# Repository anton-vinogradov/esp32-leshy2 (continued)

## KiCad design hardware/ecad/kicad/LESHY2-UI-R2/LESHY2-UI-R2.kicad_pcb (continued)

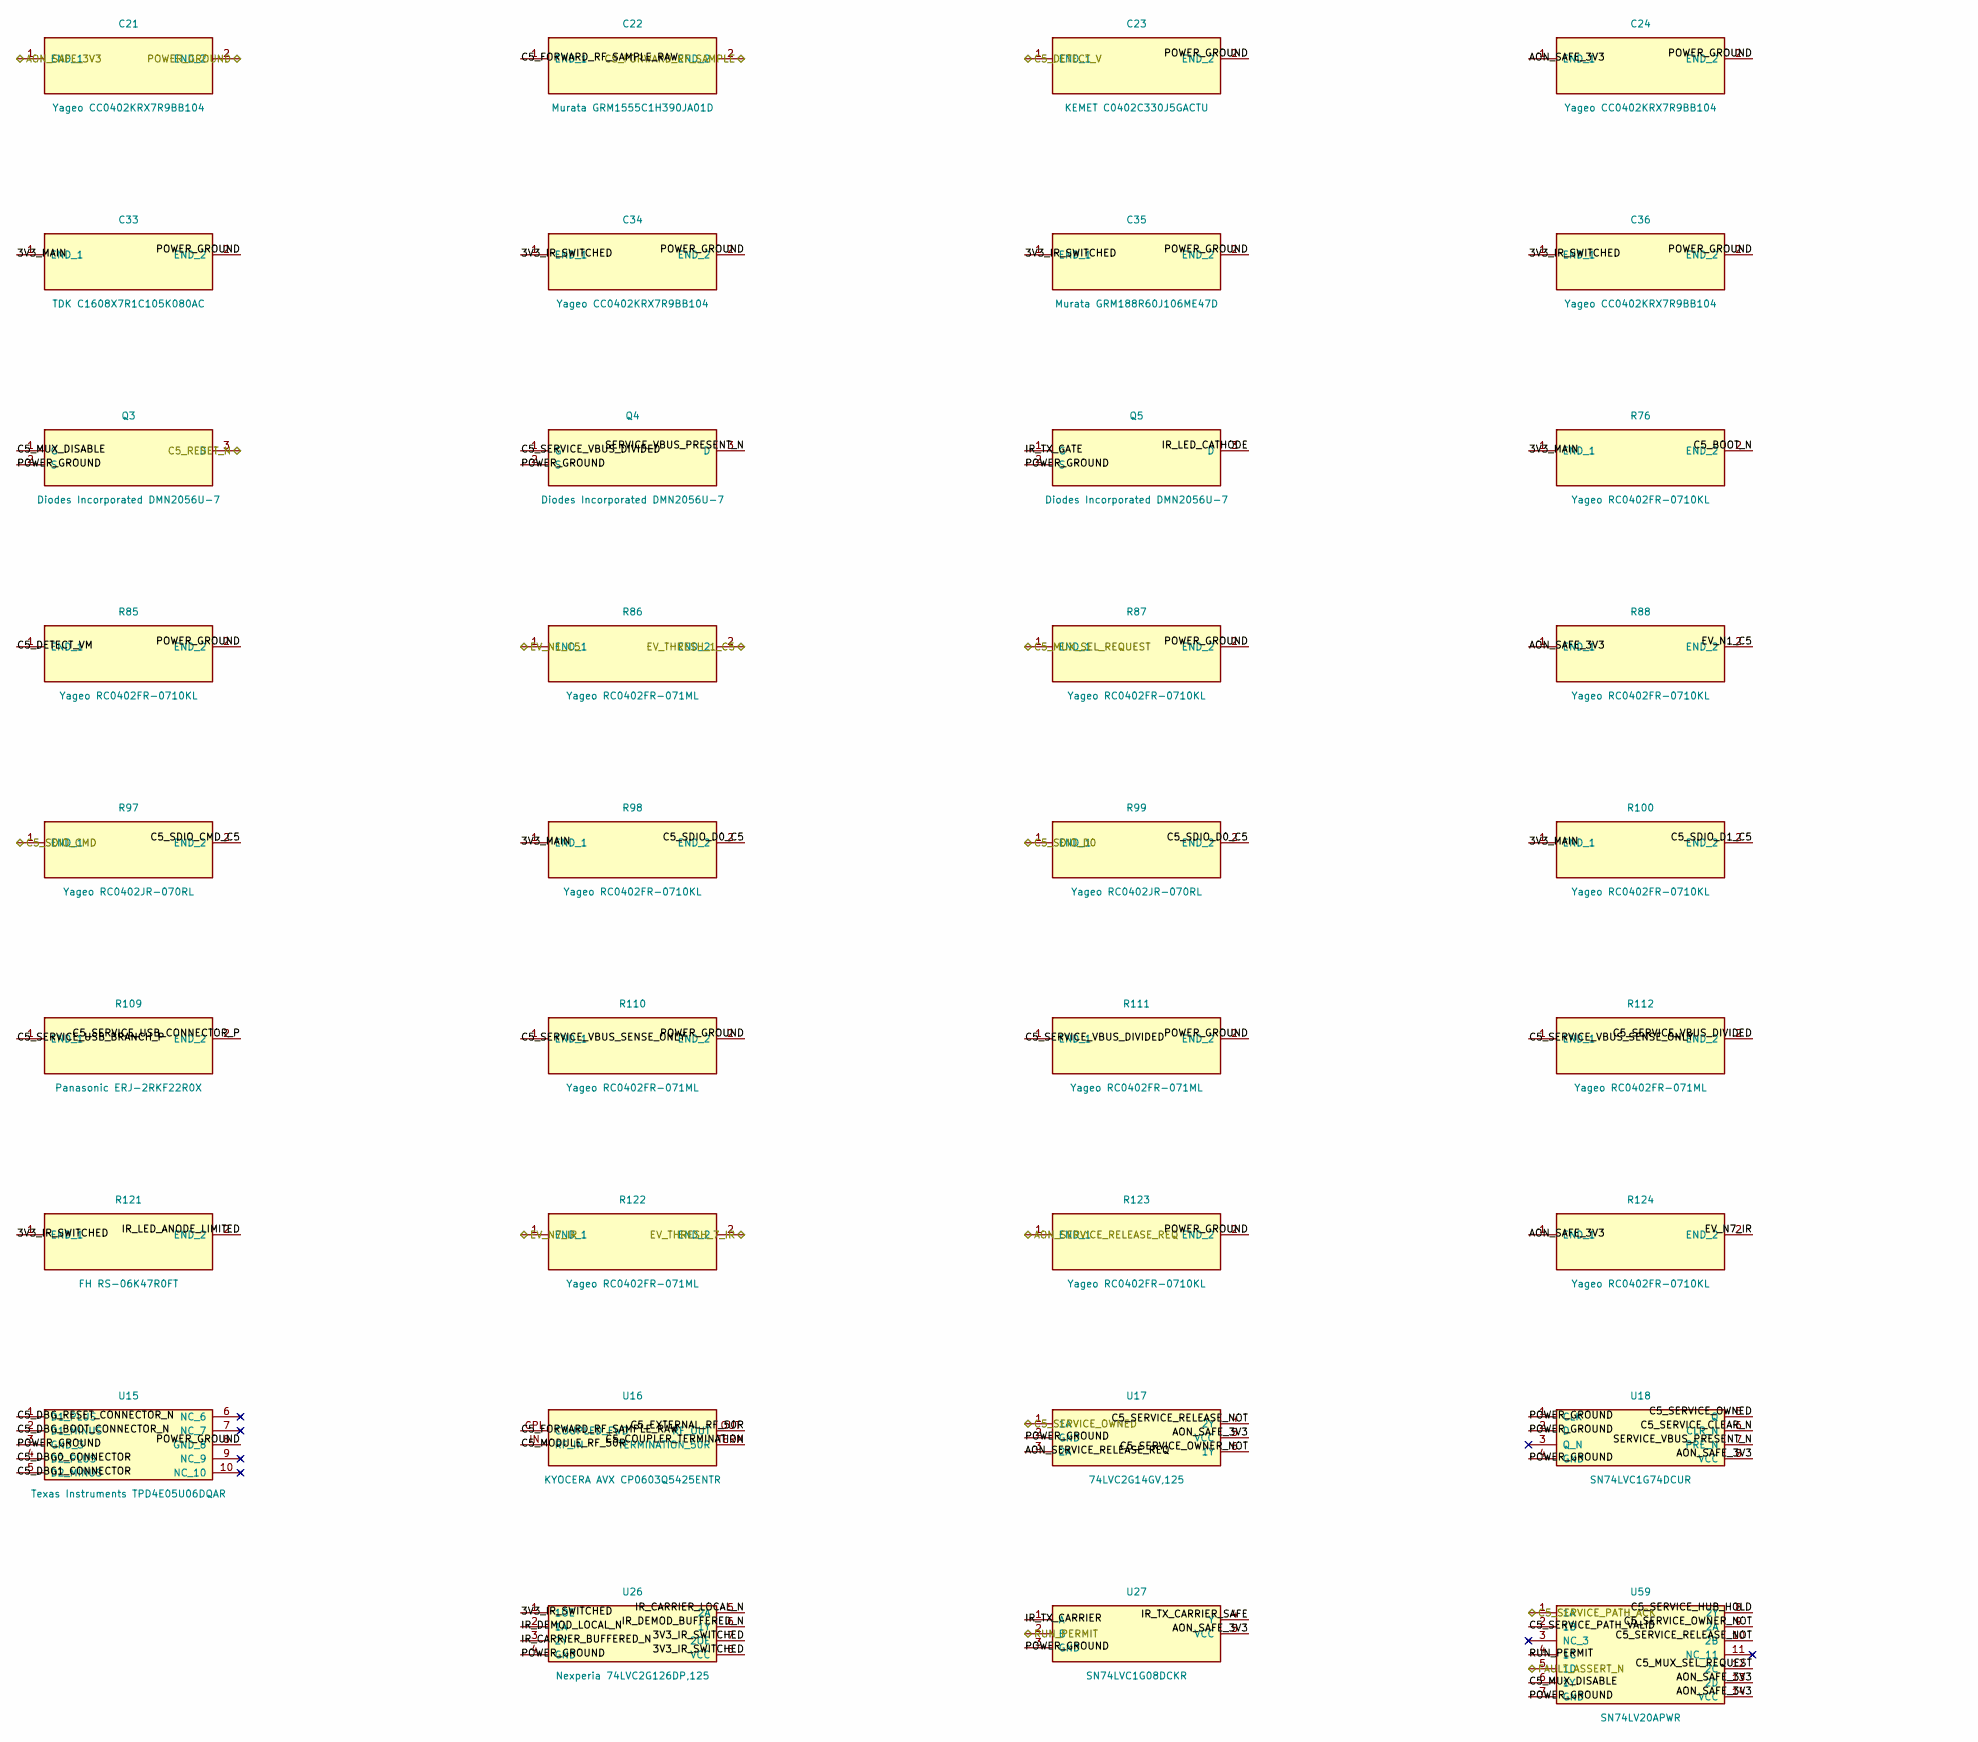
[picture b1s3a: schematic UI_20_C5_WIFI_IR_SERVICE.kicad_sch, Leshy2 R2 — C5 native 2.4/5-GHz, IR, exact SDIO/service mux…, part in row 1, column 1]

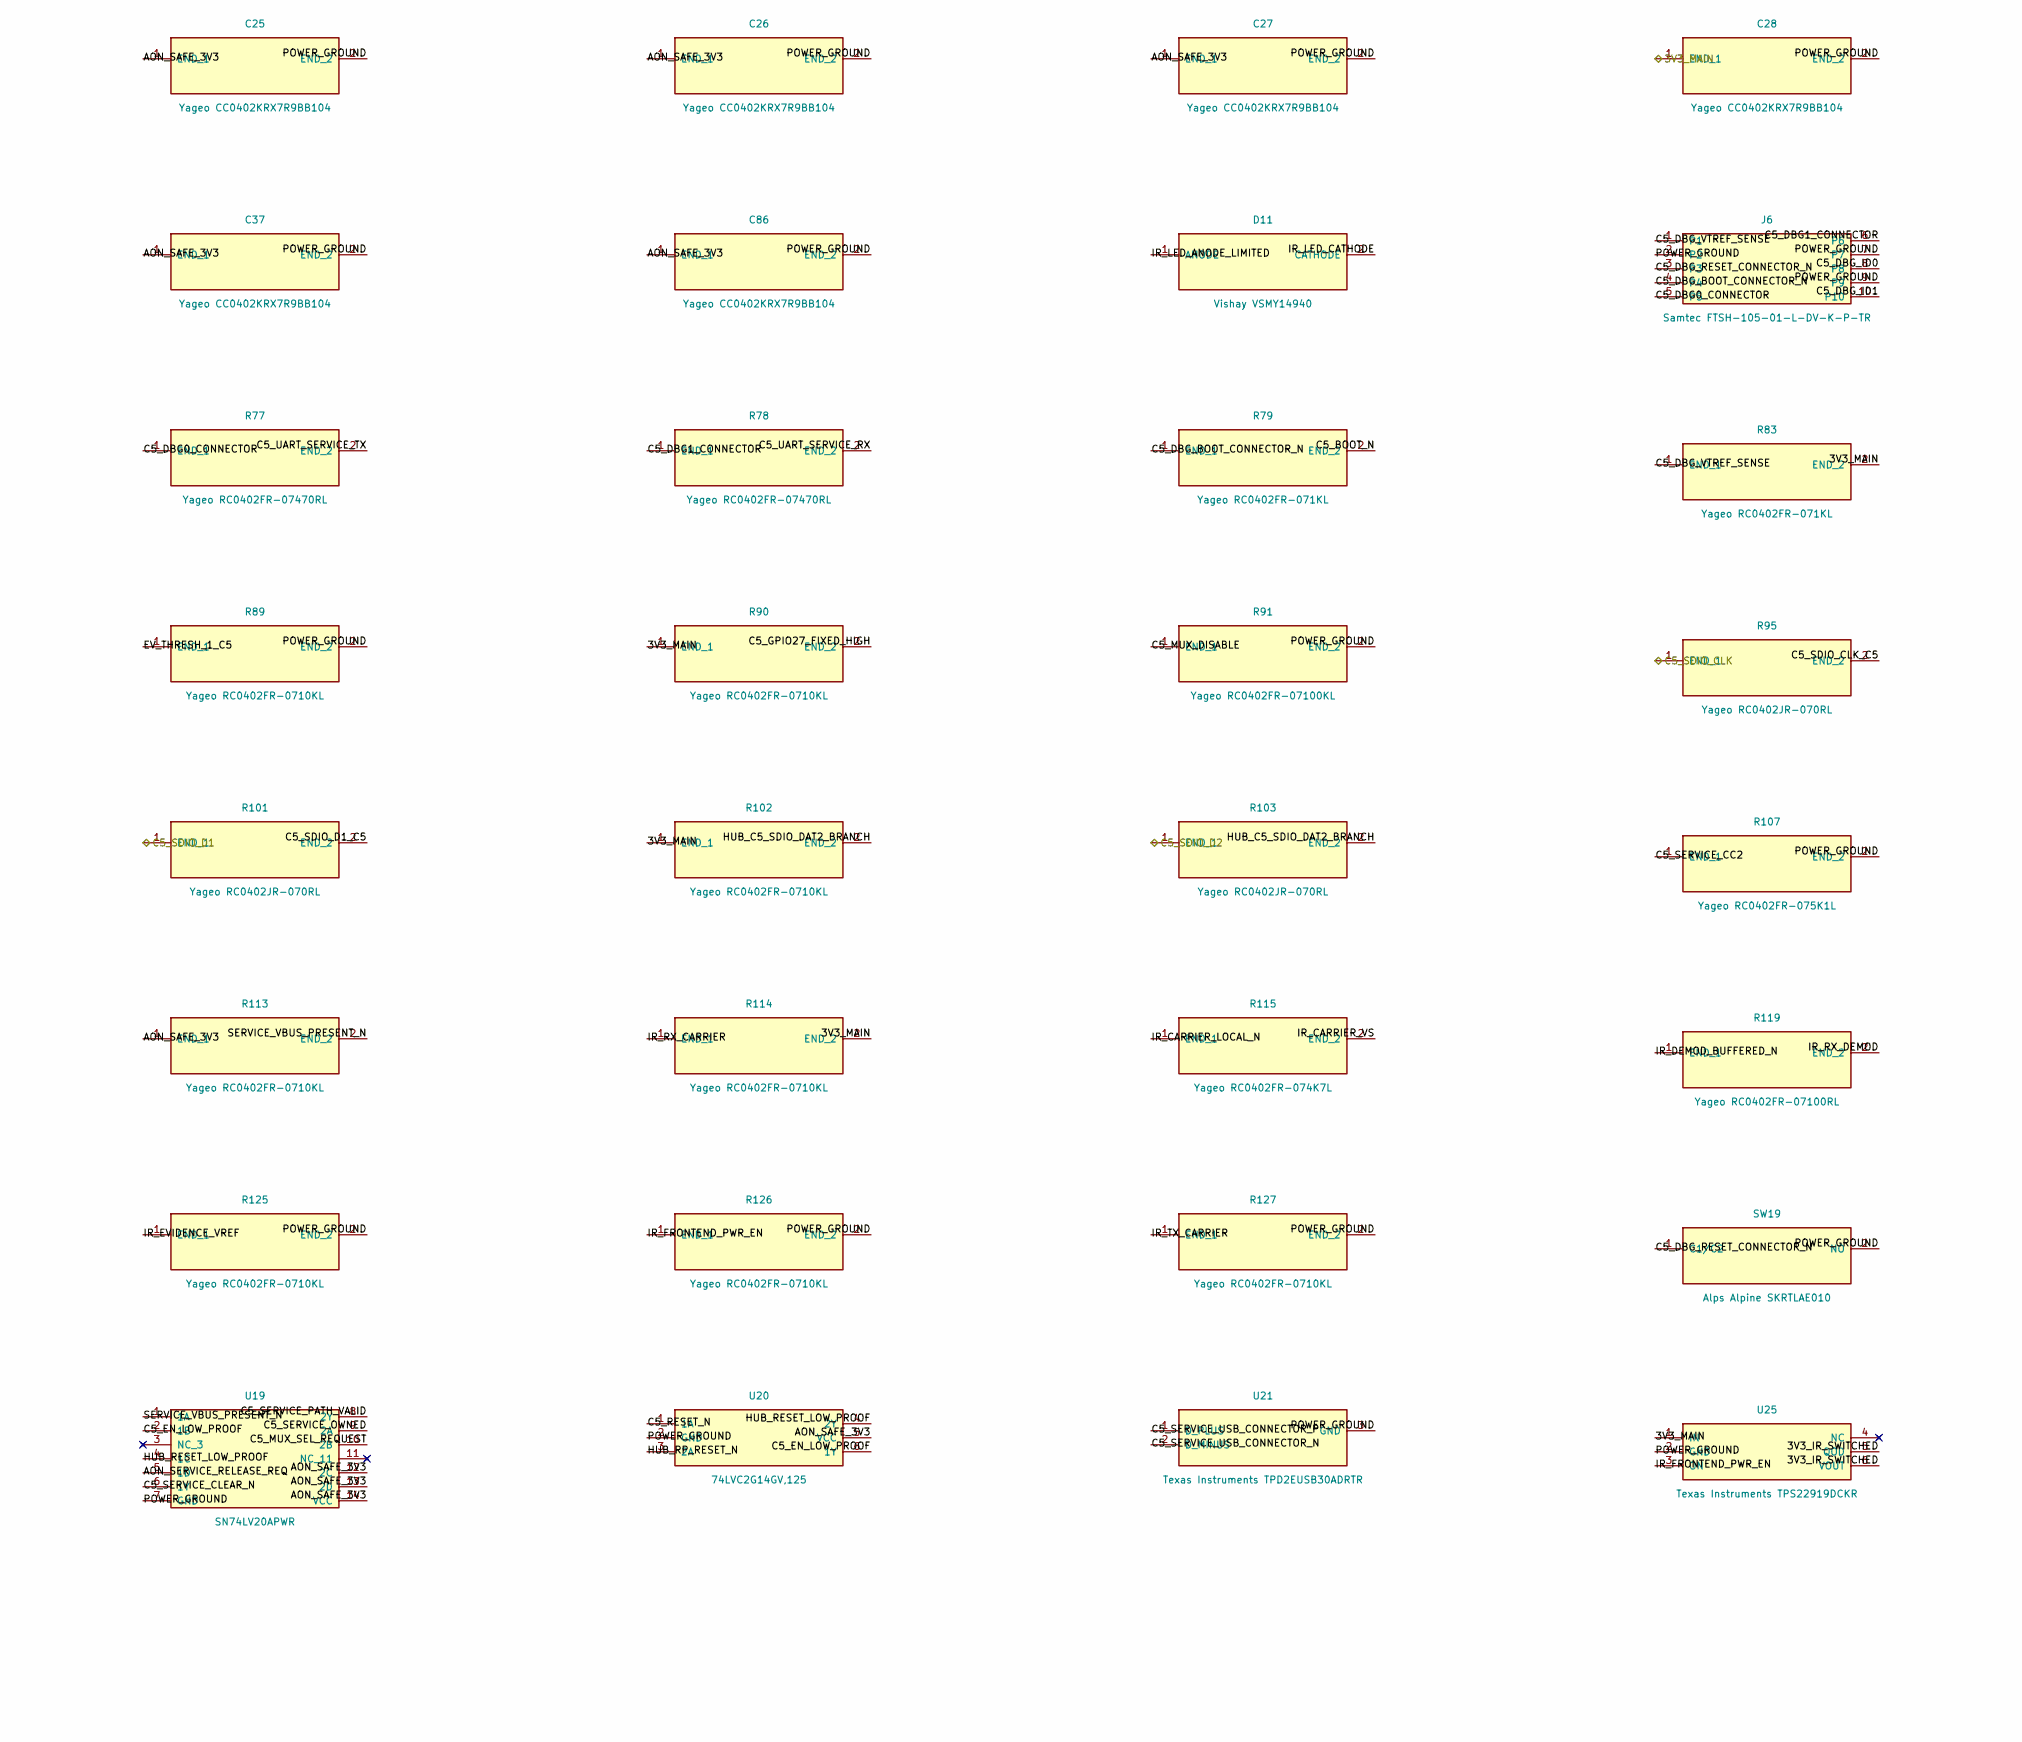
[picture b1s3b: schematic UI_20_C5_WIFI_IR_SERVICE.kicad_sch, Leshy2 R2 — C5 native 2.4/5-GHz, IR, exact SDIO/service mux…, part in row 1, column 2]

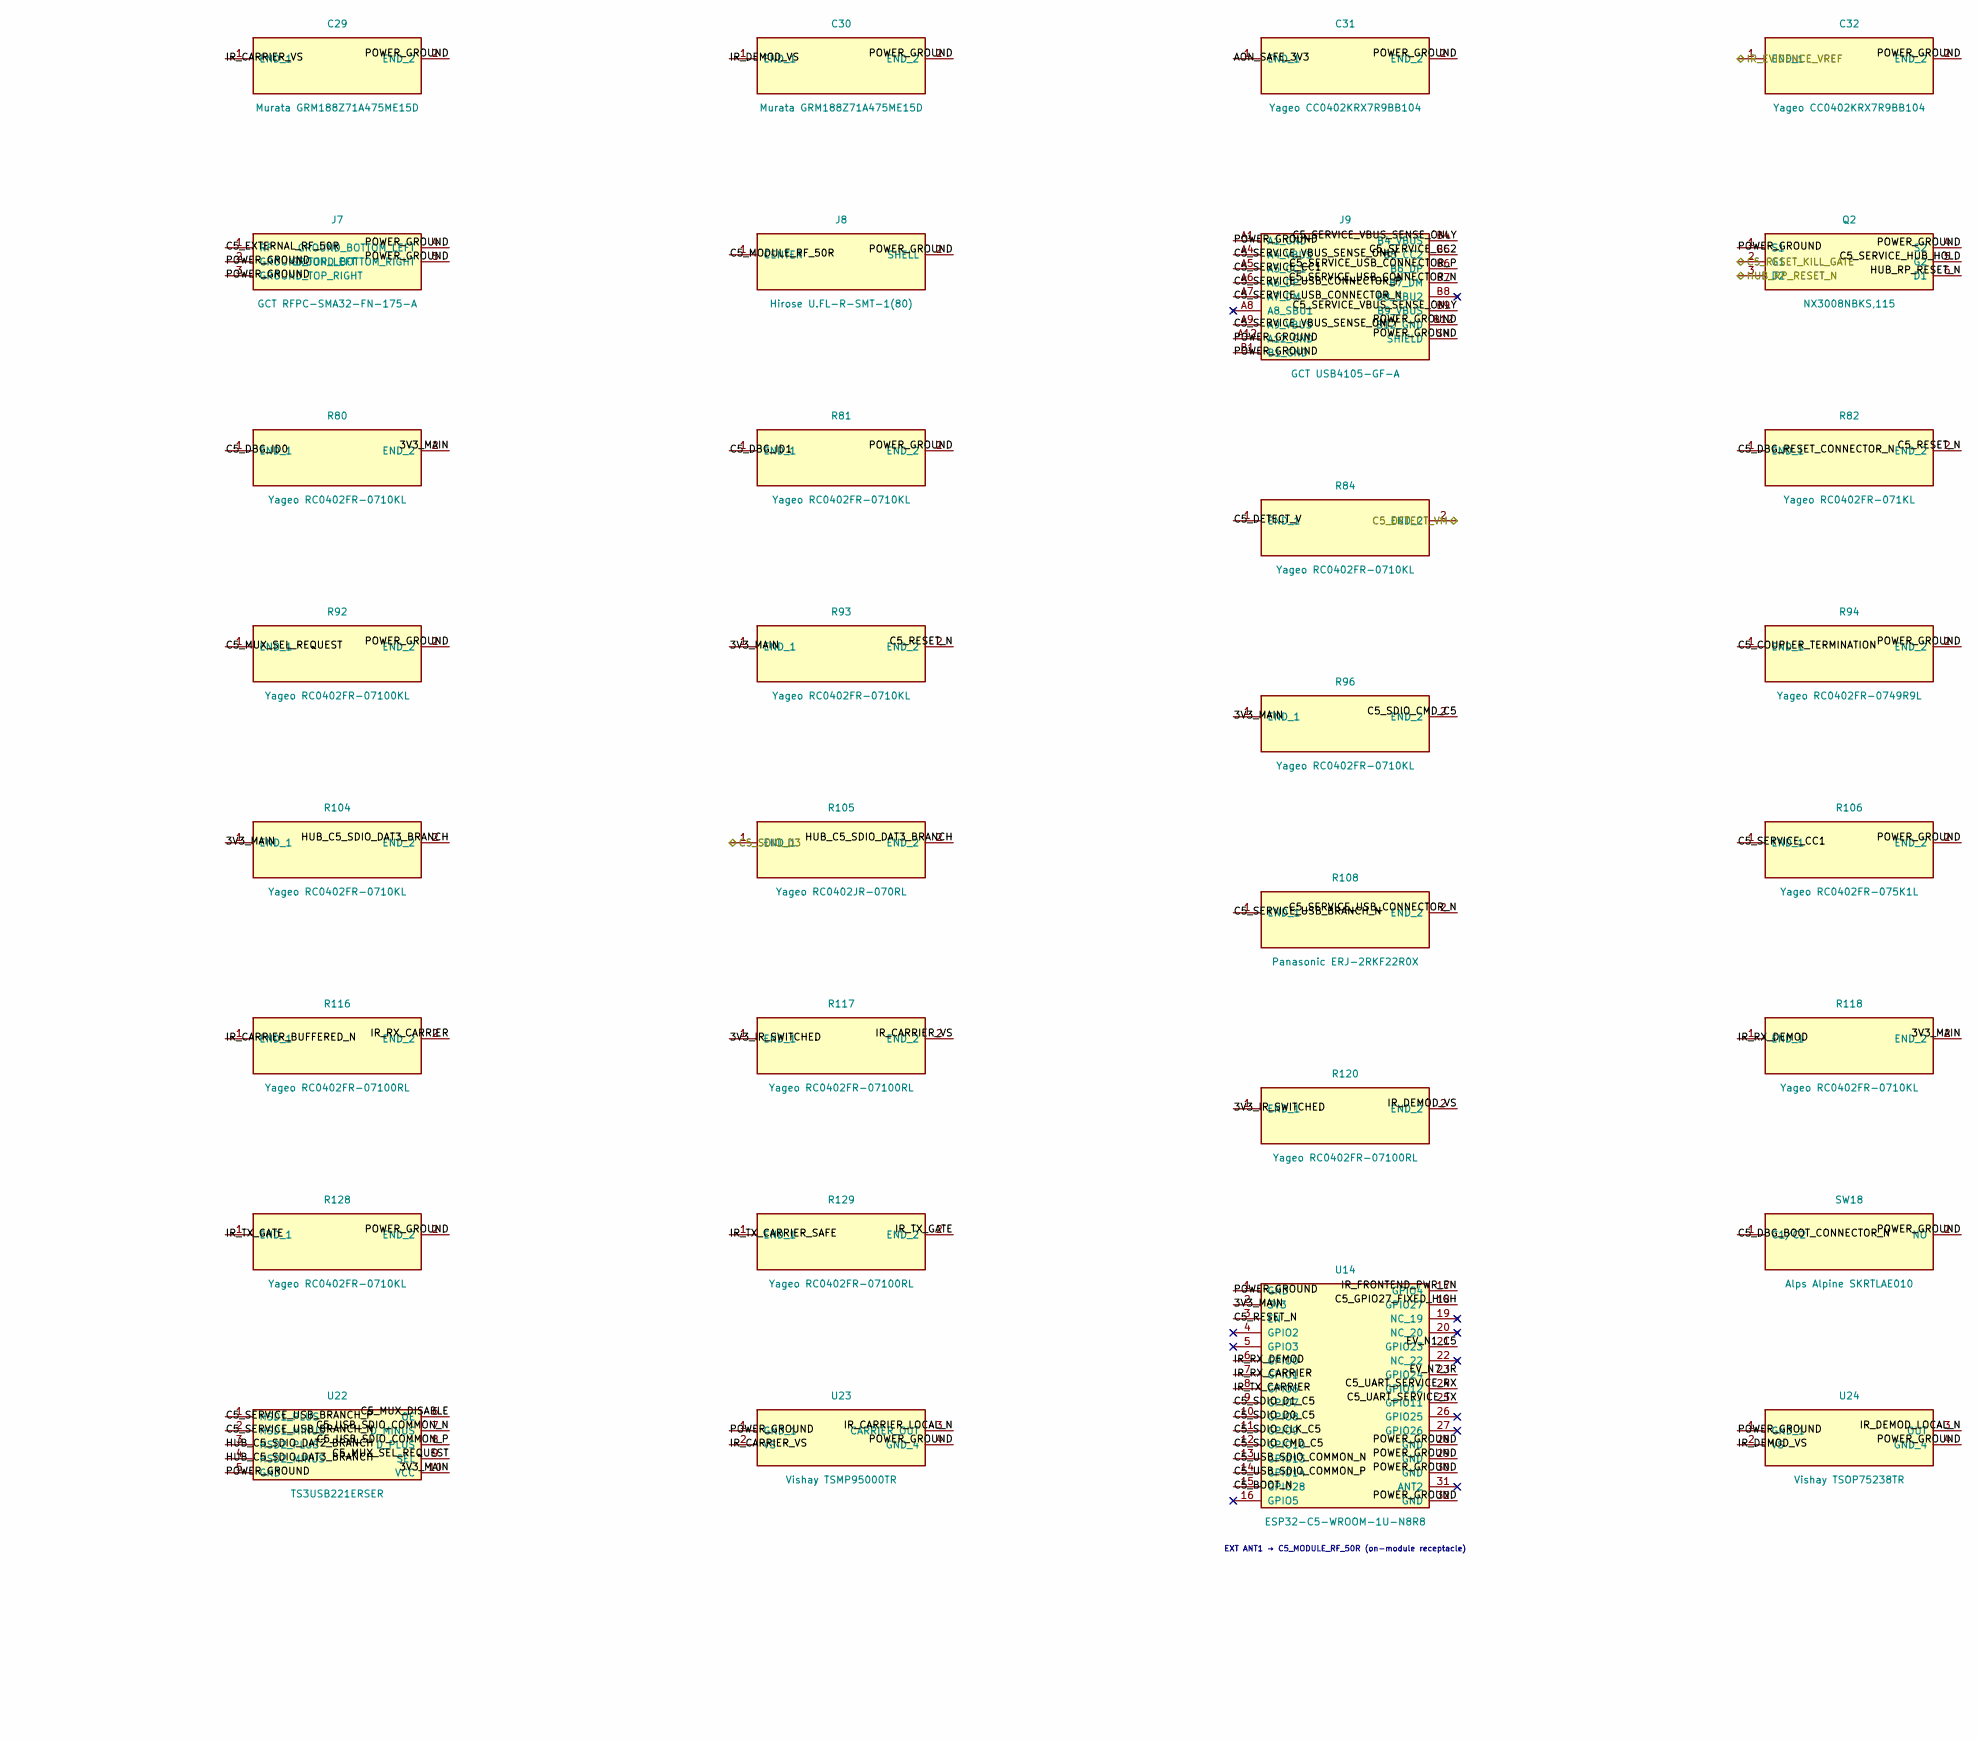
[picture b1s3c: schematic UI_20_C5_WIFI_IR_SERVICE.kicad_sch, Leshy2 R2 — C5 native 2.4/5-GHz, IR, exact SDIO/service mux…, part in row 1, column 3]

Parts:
C21, C24, C25, C26, C27, C28, C31, C32, C34, C36, C37, C86: Yageo CC0402KRX7R9BB104; C_0402_1005Metric
C22: Murata GRM1555C1H390JA01D; C_0402_1005Metric
C23: KEMET C0402C330J5GACTU; C_0402_1005Metric
C29, C30: Murata GRM188Z71A475ME15D; C_0603_1608Metric
C33: TDK C1608X7R1C105K080AC; C_0603_1608Metric
C35: Murata GRM188R60J106ME47D; C_0603_1608Metric
D11: Vishay VSMY14940; VSMY14940
J6: Samtec FTSH-105-01-L-DV-K-P-TR; FTSH-105-01-L-DV-K-P-TR
J7: GCT RFPC-SMA32-FN-175-A; RFPC-SMA32-FN-175-A
J8: Hirose U.FL-R-SMT-1(80); U.FL_Hirose_U.FL-R-SMT-1_Vertical
J9: GCT USB4105-GF-A; USB_C_Receptacle_GCT_USB4105-xx-A_16P_TopMnt_Horizontal
Q2: NX3008NBKS,115; SOT-363_SC-70-6
Q3, Q4, Q5: Diodes Incorporated DMN2056U-7; SOT-23
R76, R80, R81, R84, R85, R87, R88, R89, R90, R93, R96, R98, R100, R102, R104, R113, R114, R118, R123, R124, R125, R126, R127, R128: Yageo RC0402FR-0710KL; R_0402_1005Metric
R77, R78: Yageo RC0402FR-07470RL; R_0402_1005Metric
R79, R82, R83: Yageo RC0402FR-071KL; R_0402_1005Metric
R86, R110, R111, R112, R122: Yageo RC0402FR-071ML; R_0402_1005Metric
R91, R92: Yageo RC0402FR-07100KL; R_0402_1005Metric
R94: Yageo RC0402FR-0749R9L; R_0402_1005Metric
R95, R97, R99, R101, R103, R105: Yageo RC0402JR-070RL; R_0402_1005Metric
R106, R107: Yageo RC0402FR-075K1L; R_0402_1005Metric
R108, R109: Panasonic ERJ-2RKF22R0X; R_0402_1005Metric
R115: Yageo RC0402FR-074K7L; R_0402_1005Metric
R116, R117, R119, R120, R129: Yageo RC0402FR-07100RL; R_0402_1005Metric
R121: FH RS-06K47R0FT; R_1206_3216Metric
SW18, SW19: Alps Alpine SKRTLAE010; SW_Push_1P1T-MP_NO_Horizontal_Alps_SKRTLAE010
U14: ESP32-C5-WROOM-1U-N8R8; ESP32-C5-WROOM-1U
U15: Texas Instruments TPD4E05U06DQAR; USON-10_2.5x1.0mm_P0.5mm
U16: KYOCERA AVX CP0603Q5425ENTR; CP0603Q5425ENTR
U17, U20: 74LVC2G14GV,125; SC-74-6_1.55x2.9mm_P0.95mm
U18: SN74LVC1G74DCUR; VSSOP-8_2.3x2mm_P0.5mm
U19, U59: SN74LV20APWR; TSSOP-14_4.4x5mm_P0.65mm
U21: Texas Instruments TPD2EUSB30ADRTR; Texas_DRT-3
U22: TS3USB221ERSER; Texas_UQFN-10_1.5x2mm_P0.5mm
U23: Vishay TSMP95000TR; Vishay-Heimdall-SMD-TR
U24: Vishay TSOP75238TR; Vishay-Heimdall-SMD-TR
U25: Texas Instruments TPS22919DCKR; SOT-363_SC-70-6
U26: Nexperia 74LVC2G126DP,125; TSSOP-8_3x3mm_P0.65mm
U27: SN74LVC1G08DCKR; Texas_R-PDSO-G5_DCK-5

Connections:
/UI_10_S3_DISPLAY_TOUCH/3V3_MAIN: C28.1 (END_1), C33.1 (END_1), R76.1 (END_1), R80.2 (END_2), R83.2 (END_2), R90.1 (END_1), R93.1 (END_1), R96.1 (END_1), R98.1 (END_1), R100.1 (END_1), R102.1 (END_1), R104.1 (END_1), R114.2 (END_2), R118.2 (END_2), U14.2 (3V3), U22.10 (VCC), U25.1 (IN); also elsewhere on the board
/UI_10_S3_DISPLAY_TOUCH/AON_SAFE_3V3: C21.1 (END_1), C24.1 (END_1), C25.1 (END_1), C26.1 (END_1), C27.1 (END_1), C31.1 (END_1), C37.1 (END_1), C86.1 (END_1), R88.1 (END_1), R113.1 (END_1), R124.1 (END_1), U17.5 (VCC), U18.8 (VCC), U19.12 (2C), U19.13 (2D), U19.14 (VCC), U20.5 (VCC), U27.5 (VCC), U59.13 (2D), U59.14 (VCC); also elsewhere on the board
/UI_10_S3_DISPLAY_TOUCH/POWER_GROUND: C21.2 (END_2), C23.2 (END_2), C24.2 (END_2), C25.2 (END_2), C26.2 (END_2), C27.2 (END_2), C28.2 (END_2), C29.2 (END_2), C30.2 (END_2), C31.2 (END_2), C32.2 (END_2), C33.2 (END_2), C34.2 (END_2), C35.2 (END_2), C36.2 (END_2), C37.2 (END_2), C86.2 (END_2), J6.2, J6.7, J6.9, J7.2 (GROUND_TOP_LEFT), J7.3 (GROUND_TOP_RIGHT), J7.4 (GROUND_BOTTOM_LEFT), J7.5 (GROUND_BOTTOM_RIGHT), J8.2 (SHELL), J9.A1 (A1_GND), J9.A12 (A12_GND), J9.B1 (B1_GND), J9.B12 (B12_GND), J9.SH (SHIELD), Q2.1 (S1), Q2.4 (S2), Q3.2 (S), Q4.2 (S), Q5.2 (S), R81.2 (END_2), R85.2 (END_2), R87.2 (END_2), R89.2 (END_2), R91.2 (END_2), R92.2 (END_2), R94.2 (END_2), R106.2 (END_2), R107.2 (END_2), R110.2 (END_2), R111.2 (END_2), R123.2 (END_2), R125.2 (END_2), R126.2 (END_2), R127.2 (END_2), R128.2 (END_2), SW18.2 (NO), SW19.2 (NO), U14.1 (GND), U14.28 (GND), U14.29 (GND), U14.30 (GND), U14.32 (GND), U15.3 (GND_3), U15.8 (GND_8), U17.2 (GND), U18.1 (CLK), U18.2 (D), U18.4 (GND), U19.7 (GND), U20.2 (GND), U21.3 (GND), U22.5 (GND), U23.1 (GND_1), U23.4 (GND_4), U24.1 (GND_1), U24.4 (GND_4), U25.2 (GND), U26.4 (GND), U27.3 (GND), U59.7 (GND); also elsewhere on the board
/UI_20_C5_WIFI_IR_SERVICE/3V3_IR_SWITCHED: C34.1 (END_1), C35.1 (END_1), C36.1 (END_1), R117.1 (END_1), R120.1 (END_1), R121.1 (END_1), U25.5 (QOD), U25.6 (VOUT), U26.1 (1OE), U26.7 (2OE), U26.8 (VCC)
/UI_20_C5_WIFI_IR_SERVICE/AON_SERVICE_RELEASE_REQ: R123.1 (END_1), U17.3 (2A), U19.5 (1D); also elsewhere on the board
/UI_20_C5_WIFI_IR_SERVICE/C5_BOOT_N: R76.2 (END_2), R79.2 (END_2), U14.15 (GPIO28)
/UI_20_C5_WIFI_IR_SERVICE/C5_COUPLER_TERMINATION: R94.1 (END_1), U16.TERM (TERMINATION_50R)
/UI_20_C5_WIFI_IR_SERVICE/C5_DBG0_CONNECTOR: J6.5, R77.1 (END_1), U15.4 (D2_PLUS)
/UI_20_C5_WIFI_IR_SERVICE/C5_DBG1_CONNECTOR: J6.6, R78.1 (END_1), U15.5 (D2_MINUS)
/UI_20_C5_WIFI_IR_SERVICE/C5_DBG_BOOT_CONNECTOR_N: J6.4, R79.1 (END_1), SW18.1 (C1/C2), U15.2 (D1_MINUS)
/UI_20_C5_WIFI_IR_SERVICE/C5_DBG_ID0: J6.8, R80.1 (END_1)
/UI_20_C5_WIFI_IR_SERVICE/C5_DBG_ID1: J6.10, R81.1 (END_1)
/UI_20_C5_WIFI_IR_SERVICE/C5_DBG_RESET_CONNECTOR_N: J6.3, R82.1 (END_1), SW19.1 (C1/C2), U15.1 (D1_PLUS)
/UI_20_C5_WIFI_IR_SERVICE/C5_DBG_VTREF_SENSE: J6.1, R83.1 (END_1)
/UI_20_C5_WIFI_IR_SERVICE/C5_DETECT_V: C23.1 (END_1), R84.1 (END_1); also elsewhere on the board
/UI_20_C5_WIFI_IR_SERVICE/C5_DETECT_VM: R84.2 (END_2), R85.1 (END_1); also elsewhere on the board
/UI_20_C5_WIFI_IR_SERVICE/C5_EN_LOW_PROOF: U19.2 (1B), U20.6 (1Y)
/UI_20_C5_WIFI_IR_SERVICE/C5_EXTERNAL_RF_50R: J7.1 (RF), U16.OUT (RF_OUT)
/UI_20_C5_WIFI_IR_SERVICE/C5_FORWARD_RF_SAMPLE: C22.2 (END_2); also elsewhere on the board
/UI_20_C5_WIFI_IR_SERVICE/C5_FORWARD_RF_SAMPLE_RAW: C22.1 (END_1), U16.CPL (COUPLED_FWD)
/UI_20_C5_WIFI_IR_SERVICE/C5_GPIO27_FIXED_HIGH: R90.2 (END_2), U14.18 (GPIO27)
/UI_20_C5_WIFI_IR_SERVICE/C5_MODULE_RF_50R: J8.1 (CENTER), U16.IN (RF_IN)
/UI_20_C5_WIFI_IR_SERVICE/C5_MUX_DISABLE: Q3.1 (G), R91.1 (END_1), U22.6 (OE), U59.6 (1Y)
/UI_20_C5_WIFI_IR_SERVICE/C5_MUX_SEL_REQUEST: R87.1 (END_1), R92.1 (END_1), U19.10 (2B), U22.9 (SEL), U59.12 (2C); also elsewhere on the board
/UI_20_C5_WIFI_IR_SERVICE/C5_RESET_N: Q3.3 (D), R82.2 (END_2), R93.2 (END_2), U14.3 (EN), U20.1 (1A); also elsewhere on the board
/UI_20_C5_WIFI_IR_SERVICE/C5_SDIO_CLK: R95.1 (END_1); also elsewhere on the board
/UI_20_C5_WIFI_IR_SERVICE/C5_SDIO_CLK_C5: R95.2 (END_2), U14.11 (GPIO9)
/UI_20_C5_WIFI_IR_SERVICE/C5_SDIO_CMD: R97.1 (END_1); also elsewhere on the board
/UI_20_C5_WIFI_IR_SERVICE/C5_SDIO_CMD_C5: R96.2 (END_2), R97.2 (END_2), U14.12 (GPIO10)
/UI_20_C5_WIFI_IR_SERVICE/C5_SDIO_D0: R99.1 (END_1); also elsewhere on the board
/UI_20_C5_WIFI_IR_SERVICE/C5_SDIO_D0_C5: R98.2 (END_2), R99.2 (END_2), U14.10 (GPIO8)
/UI_20_C5_WIFI_IR_SERVICE/C5_SDIO_D1: R101.1 (END_1); also elsewhere on the board
/UI_20_C5_WIFI_IR_SERVICE/C5_SDIO_D1_C5: R100.2 (END_2), R101.2 (END_2), U14.9 (GPIO7)
/UI_20_C5_WIFI_IR_SERVICE/C5_SDIO_D2: R103.1 (END_1); also elsewhere on the board
/UI_20_C5_WIFI_IR_SERVICE/C5_SDIO_D3: R105.1 (END_1); also elsewhere on the board
/UI_20_C5_WIFI_IR_SERVICE/C5_SERVICE_CC1: J9.A5 (A5_CC1), R106.1 (END_1)
/UI_20_C5_WIFI_IR_SERVICE/C5_SERVICE_CC2: J9.B5 (B5_CC2), R107.1 (END_1)
/UI_20_C5_WIFI_IR_SERVICE/C5_SERVICE_CLEAR_N: U18.6 (CLR_N), U19.6 (1Y)
/UI_20_C5_WIFI_IR_SERVICE/C5_SERVICE_HUB_HOLD: Q2.5 (G2), U59.8 (2Y)
/UI_20_C5_WIFI_IR_SERVICE/C5_SERVICE_OWNED: U17.1 (1A), U18.5 (Q), U19.9 (2A); also elsewhere on the board
/UI_20_C5_WIFI_IR_SERVICE/C5_SERVICE_OWNER_NOT: U17.6 (1Y), U59.9 (2A)
/UI_20_C5_WIFI_IR_SERVICE/C5_SERVICE_PATH_ACK: U59.1 (1A); also elsewhere on the board
/UI_20_C5_WIFI_IR_SERVICE/C5_SERVICE_PATH_VALID: U19.8 (2Y), U59.2 (1B)
/UI_20_C5_WIFI_IR_SERVICE/C5_SERVICE_RELEASE_NOT: U17.4 (2Y), U59.10 (2B)
/UI_20_C5_WIFI_IR_SERVICE/C5_SERVICE_USB_BRANCH_N: R108.1 (END_1), U22.2 (HSD1_MINUS)
/UI_20_C5_WIFI_IR_SERVICE/C5_SERVICE_USB_BRANCH_P: R109.1 (END_1), U22.1 (HSD1_PLUS)
/UI_20_C5_WIFI_IR_SERVICE/C5_SERVICE_USB_CONNECTOR_N: J9.A7 (A7_DM), J9.B7 (B7_DM), R108.2 (END_2), U21.2 (D_MINUS)
/UI_20_C5_WIFI_IR_SERVICE/C5_SERVICE_USB_CONNECTOR_P: J9.A6 (A6_DP), J9.B6 (B6_DP), R109.2 (END_2), U21.1 (D_PLUS)
/UI_20_C5_WIFI_IR_SERVICE/C5_SERVICE_VBUS_DIVIDED: Q4.1 (G), R111.1 (END_1), R112.2 (END_2)
/UI_20_C5_WIFI_IR_SERVICE/C5_SERVICE_VBUS_SENSE_ONLY: J9.A4 (A4_VBUS), J9.A9 (A9_VBUS), J9.B4 (B4_VBUS), J9.B9 (B9_VBUS), R110.1 (END_1), R112.1 (END_1)
/UI_20_C5_WIFI_IR_SERVICE/C5_UART_SERVICE_RX: R78.2 (END_2), U14.24 (GPIO12)
/UI_20_C5_WIFI_IR_SERVICE/C5_UART_SERVICE_TX: R77.2 (END_2), U14.25 (GPIO11)
/UI_20_C5_WIFI_IR_SERVICE/C5_USB_SDIO_COMMON_N: U14.13 (GPIO13), U22.7 (D_MINUS)
/UI_20_C5_WIFI_IR_SERVICE/C5_USB_SDIO_COMMON_P: U14.14 (GPIO14), U22.8 (D_PLUS)
/UI_20_C5_WIFI_IR_SERVICE/EV_N1_C5: R86.1 (END_1), R88.2 (END_2), U14.21 (GPIO23); also elsewhere on the board
/UI_20_C5_WIFI_IR_SERVICE/EV_N7_IR: R122.1 (END_1), R124.2 (END_2), U14.23 (GPIO24); also elsewhere on the board
/UI_20_C5_WIFI_IR_SERVICE/EV_THRESH_1_C5: R86.2 (END_2), R89.1 (END_1); also elsewhere on the board
/UI_20_C5_WIFI_IR_SERVICE/FAULT_ASSERT_N: U59.5 (1D); also elsewhere on the board
/UI_20_C5_WIFI_IR_SERVICE/HUB_C5_SDIO_DAT2_BRANCH: R102.2 (END_2), R103.2 (END_2), U22.3 (HSD2_PLUS)
/UI_20_C5_WIFI_IR_SERVICE/HUB_C5_SDIO_DAT3_BRANCH: R104.2 (END_2), R105.2 (END_2), U22.4 (HSD2_MINUS)
/UI_20_C5_WIFI_IR_SERVICE/HUB_RESET_LOW_PROOF: U19.4 (1C), U20.4 (2Y)
/UI_20_C5_WIFI_IR_SERVICE/HUB_RP_RESET_N: Q2.3 (D2), Q2.6 (D1), U20.3 (2A); also elsewhere on the board
/UI_20_C5_WIFI_IR_SERVICE/IR_CARRIER_BUFFERED_N: R116.1 (END_1), U26.3 (2Y)
/UI_20_C5_WIFI_IR_SERVICE/IR_CARRIER_LOCAL_N: R115.1 (END_1), U23.3 (CARRIER_OUT), U26.5 (2A)
/UI_20_C5_WIFI_IR_SERVICE/IR_CARRIER_VS: C29.1 (END_1), R115.2 (END_2), R117.2 (END_2), U23.2 (VS)
/UI_20_C5_WIFI_IR_SERVICE/IR_DEMOD_BUFFERED_N: R119.1 (END_1), U26.6 (1Y)
/UI_20_C5_WIFI_IR_SERVICE/IR_DEMOD_LOCAL_N: U24.3 (OUT), U26.2 (1A)
/UI_20_C5_WIFI_IR_SERVICE/IR_DEMOD_VS: C30.1 (END_1), R120.2 (END_2), U24.2 (VS)
/UI_20_C5_WIFI_IR_SERVICE/IR_EVIDENCE_VREF: C32.1 (END_1), R125.1 (END_1); also elsewhere on the board
/UI_20_C5_WIFI_IR_SERVICE/IR_FRONTEND_PWR_EN: R126.1 (END_1), U14.17 (GPIO4), U25.3 (ON)
/UI_20_C5_WIFI_IR_SERVICE/IR_LED_ANODE_LIMITED: D11.1 (ANODE), R121.2 (END_2)
/UI_20_C5_WIFI_IR_SERVICE/IR_LED_CATHODE: D11.2 (CATHODE), Q5.3 (D)
/UI_20_C5_WIFI_IR_SERVICE/IR_RX_CARRIER: R114.1 (END_1), R116.2 (END_2), U14.7 (GPIO1)
/UI_20_C5_WIFI_IR_SERVICE/IR_RX_DEMOD: R118.1 (END_1), R119.2 (END_2), U14.6 (GPIO0)
/UI_20_C5_WIFI_IR_SERVICE/IR_TX_CARRIER: R127.1 (END_1), U14.8 (GPIO6), U27.1 (A)
/UI_20_C5_WIFI_IR_SERVICE/IR_TX_CARRIER_SAFE: R129.1 (END_1), U27.4 (Y)
/UI_20_C5_WIFI_IR_SERVICE/IR_TX_GATE: Q5.1 (G), R128.1 (END_1), R129.2 (END_2)
/UI_20_C5_WIFI_IR_SERVICE/RUN_PERMIT: U27.2 (B), U59.4 (1C); also elsewhere on the board
/UI_20_C5_WIFI_IR_SERVICE/SERVICE_VBUS_PRESENT_N: Q4.3 (D), R113.2 (END_2), U18.7 (PRE_N), U19.1 (1A)
/UI_50_FRONT_POWER_SAFETY/C5_RESET_KILL_GATE: Q2.2 (G1); also elsewhere on the board
/UI_50_FRONT_POWER_SAFETY/EV_THRESH_7_IR: R122.2 (END_2); also elsewhere on the board

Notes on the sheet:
EXT ANT1 → C5_MODULE_RF_50R (on-module receptacle)
